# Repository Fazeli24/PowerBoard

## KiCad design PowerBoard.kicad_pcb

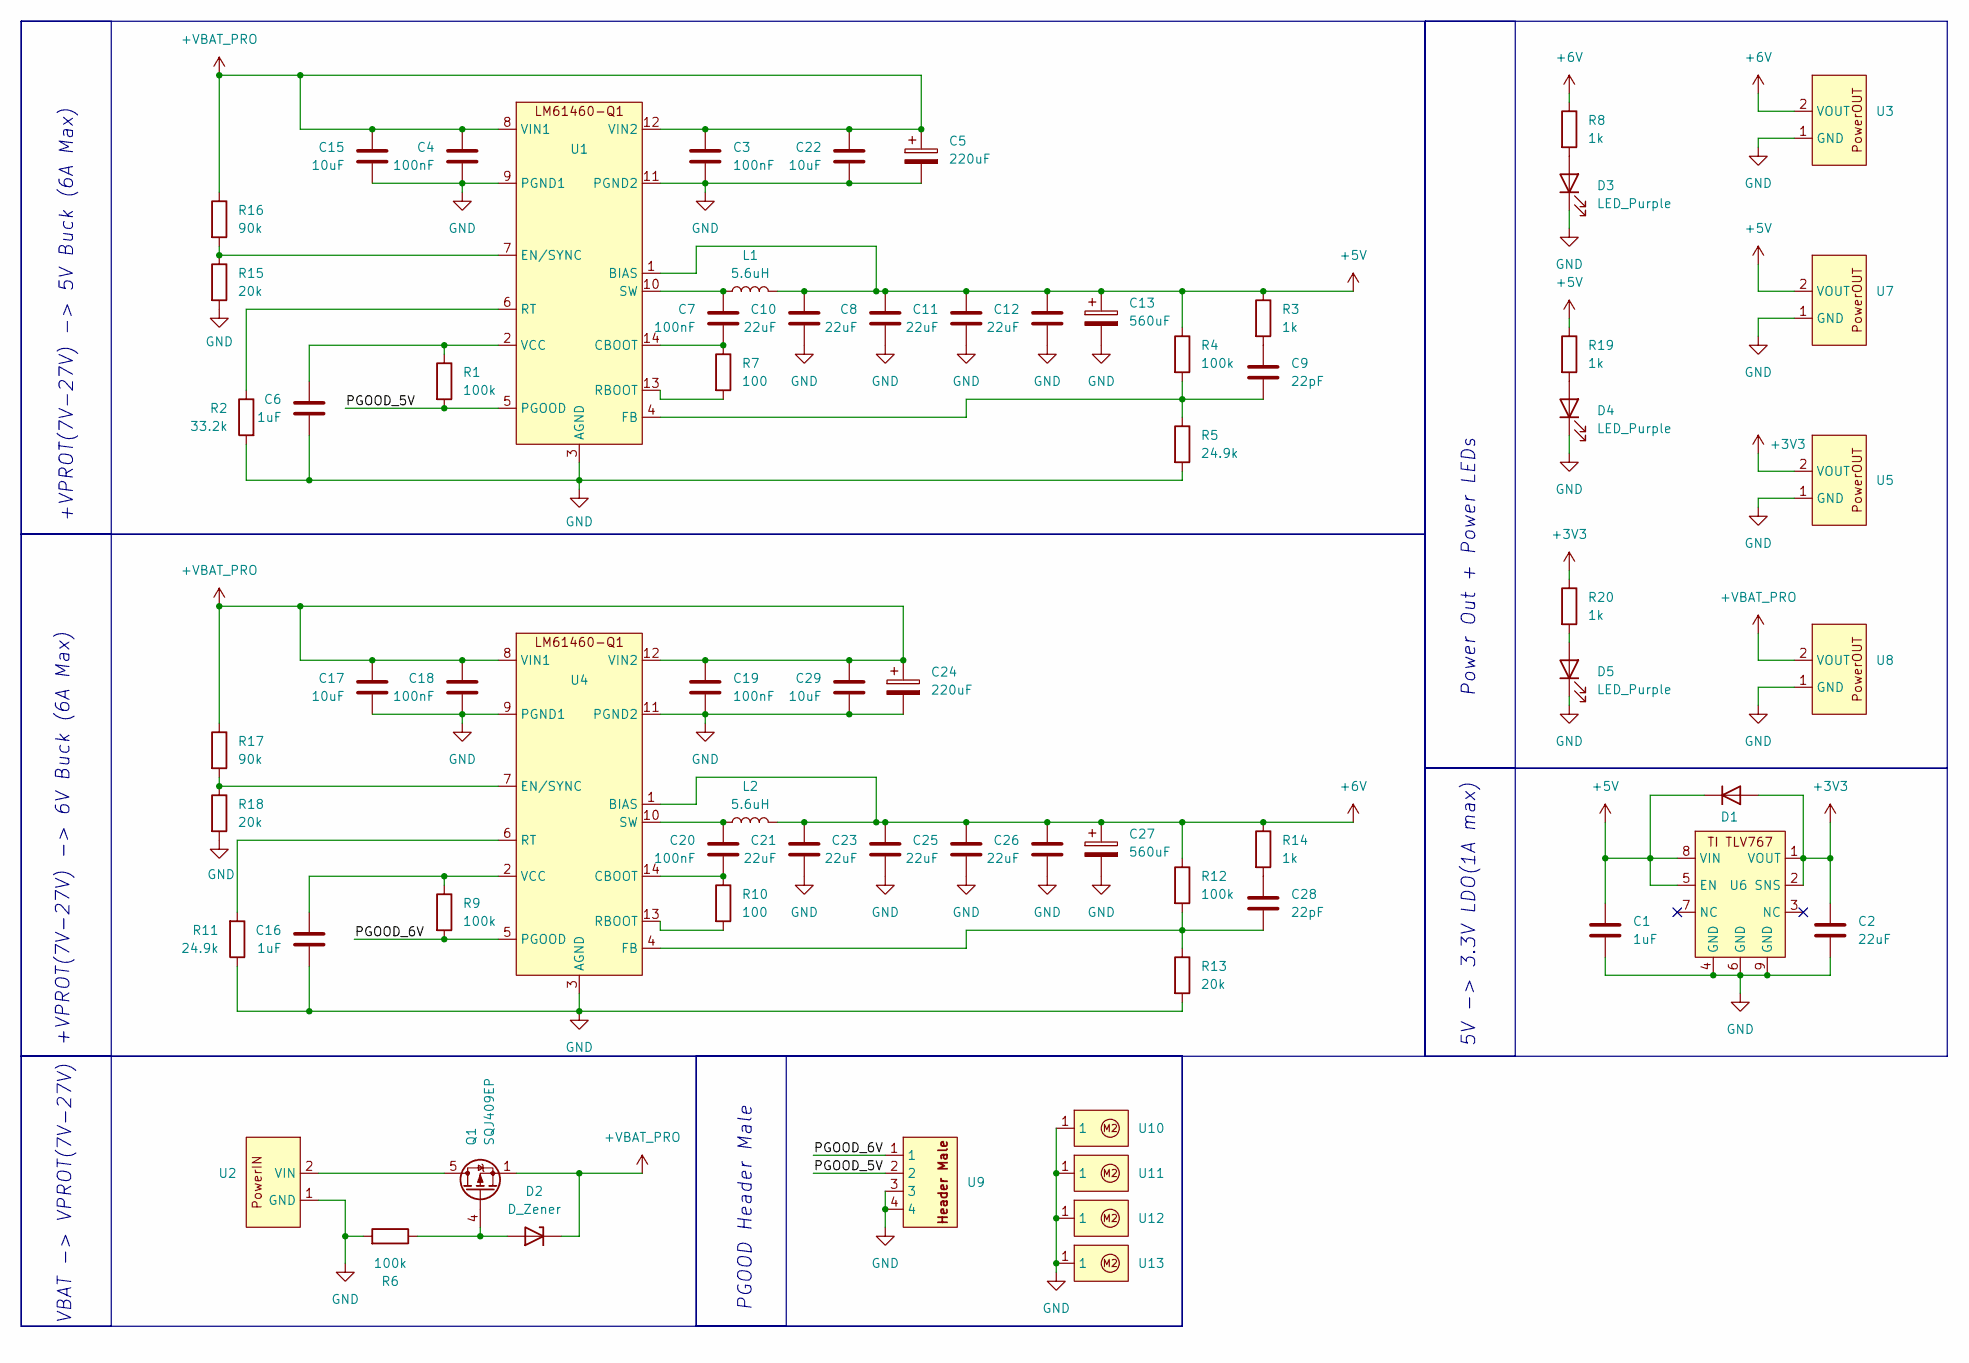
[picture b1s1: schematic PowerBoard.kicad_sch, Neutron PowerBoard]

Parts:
C1, C6, C16: 1uF; C_0603_1608Metric; LCSC Part # C59782
C2, C8, C10, C11, C12, C21, C23, C25, C26: 22uF; C_1210_3225Metric; LCSC Part # C55530
C3, C4, C7, C18, C19, C20: 100nF; C_0603_1608Metric; LCSC Part # C1591
C5, C24: 220uF; CP_Elec_8x10.5; LCSC Part # C278406
C9, C28: 22pF; C_0603_1608Metric; LCSC Part # C1653
C13, C27: 560uF; CP_Elec_8x10.5; LCSC Part # C497589
C15, C17, C22, C29: 10uF; C_1206_3216Metric; LCSC Part # C89632
D1: D; SOT-23-3; LCSC Part # C545546
D2: D_Zener; SOT-23; LCSC Part # C108437
D3, D4, D5: LED_Purple; LED_0603_1608Metric; LCSC Part # C7496831
L1, L2: 5.6uH; Inductor_11.5_10; LCSC Part # C49140770
Q1: SQJ409EP; PowerPAK_SO-8L_Single; LCSC Part # C727776
R1, R4, R6, R9, R12: 100k; R_0603_1608Metric; LCSC Part # C2906980
R2: 33.2k; R_0603_1608Metric; LCSC Part # C2933200
R3, R8, R14, R19, R20: 1k; R_0603_1608Metric; LCSC Part # C2907002
R5, R11: 24.9k; R_0603_1608Metric; LCSC Part # C2930080
R7, R10: 100; R_0603_1608Metric; LCSC Part # C2906981
R13, R15, R18: 20k; R_0603_1608Metric; LCSC Part # C2907011
R16, R17: 90k; R_0603_1608Metric; LCSC Part # C2907077
U1, U4: VQFN-HR14_RJR_TEX; LCSC Part # C2876600
U2, U3, U7, U8: HighCurrentPad
U5: LowCurrentPad
U6: HVSSOP-8-1EP_3x3mm_P0.65mm_EP1.57x1.89mm; LCSC Part # C2873382
U9: 4x1_2.54mmPitch
U10, U11, U12, U13: Unbenannt

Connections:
+3V3: C2.1, D1.2 (A), R20.1, U5.2 (VOUT), U6.1 (VOUT), U6.2 (SNS)
+5V: C1.1, C8.1, C10.1, C11.1, C12.1, C13.1, D1.1 (K), L1.2, R3.1, R4.1, R19.1, U1.1 (BIAS), U6.5 (EN), U6.8 (VIN), U7.2 (VOUT)
+6V: C21.1, C23.1, C25.1, C26.1, C27.1, L2.2, R8.1, R12.1, R14.1, U3.2 (VOUT), U4.1 (BIAS)
+VBAT_PRO: C3.1, C4.1, C5.1, C15.1, C17.1, C18.1, C19.1, C22.1, C24.1, C29.1, D2.1 (K), Q1.1 (S), Q1.2 (S), Q1.3 (S), R16.1, R17.1, U1.8 (VIN1), U1.12 (VIN2), U4.8 (VIN1), U4.12 (VIN2), U8.2 (VOUT)
/PGOOD_5V: R1.2, U1.5 (PGOOD), U9.2
/PGOOD_6V: R9.2, U4.5 (PGOOD), U9.1
GND: C1.2, C2.2, C3.2, C4.2, C5.2, C6.2, C8.2, C10.2, C11.2, C12.2, C13.2, C15.2, C16.2, C17.2, C18.2, C19.2, C21.2, C22.2, C23.2, C24.2, C25.2, C26.2, C27.2, C29.2, D3.1 (K), D4.1 (K), D5.1 (K), R2.2, R5.2, R6.2, R11.1, R13.2, R15.2, R18.2, U1.3 (AGND), U1.9 (PGND1), U1.11 (PGND2), U2.1 (GND), U3.1 (GND), U4.3 (AGND), U4.9 (PGND1), U4.11 (PGND2), U5.1 (GND), U6.4 (GND), U6.6 (GND), U6.9 (GND), U7.1 (GND), U8.1 (GND), U9.3, U9.4, U10.1 (1_1), U11.1 (1_1), U12.1 (1_1), U13.1 (1_1)
unnamed: C9.1, R3.2
unnamed: C28.1, R14.2
unnamed: D2.2 (A), Q1.4 (G), R6.1
unnamed: D3.2 (A), R8.2
unnamed: D4.2 (A), R19.2
unnamed: D5.2 (A), R20.2
unnamed: Q1.5 (D), U2.2 (VIN)
unnamed: C7.2, R7.1, U1.14 (CBOOT)
unnamed: R15.1, R16.2, U1.7 (EN/SYNC)
unnamed: C9.2, R4.2, R5.1, U1.4 (FB)
unnamed: R7.2, U1.13 (RBOOT)
unnamed: R2.1, U1.6 (RT)
unnamed: C7.1, L1.1, U1.10 (SW)
unnamed: C6.1, R1.1, U1.2 (VCC)
unnamed: C20.2, R10.1, U4.14 (CBOOT)
unnamed: R17.2, R18.1, U4.7 (EN/SYNC)
unnamed: C28.2, R12.2, R13.1, U4.4 (FB)
unnamed: R10.2, U4.13 (RBOOT)
unnamed: R11.2, U4.6 (RT)
unnamed: C20.1, L2.1, U4.10 (SW)
unnamed: C16.1, R9.1, U4.2 (VCC)

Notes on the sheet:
VBAT -> VPROT(7V-27V)
PGOOD Header Male
5V -> 3.3V LDO(1A max)
Power Out + Power LEDs
+VPROT(7V-27V) -> 5V Buck (6A Max)
+VPROT(7V-27V) -> 6V Buck (6A Max)

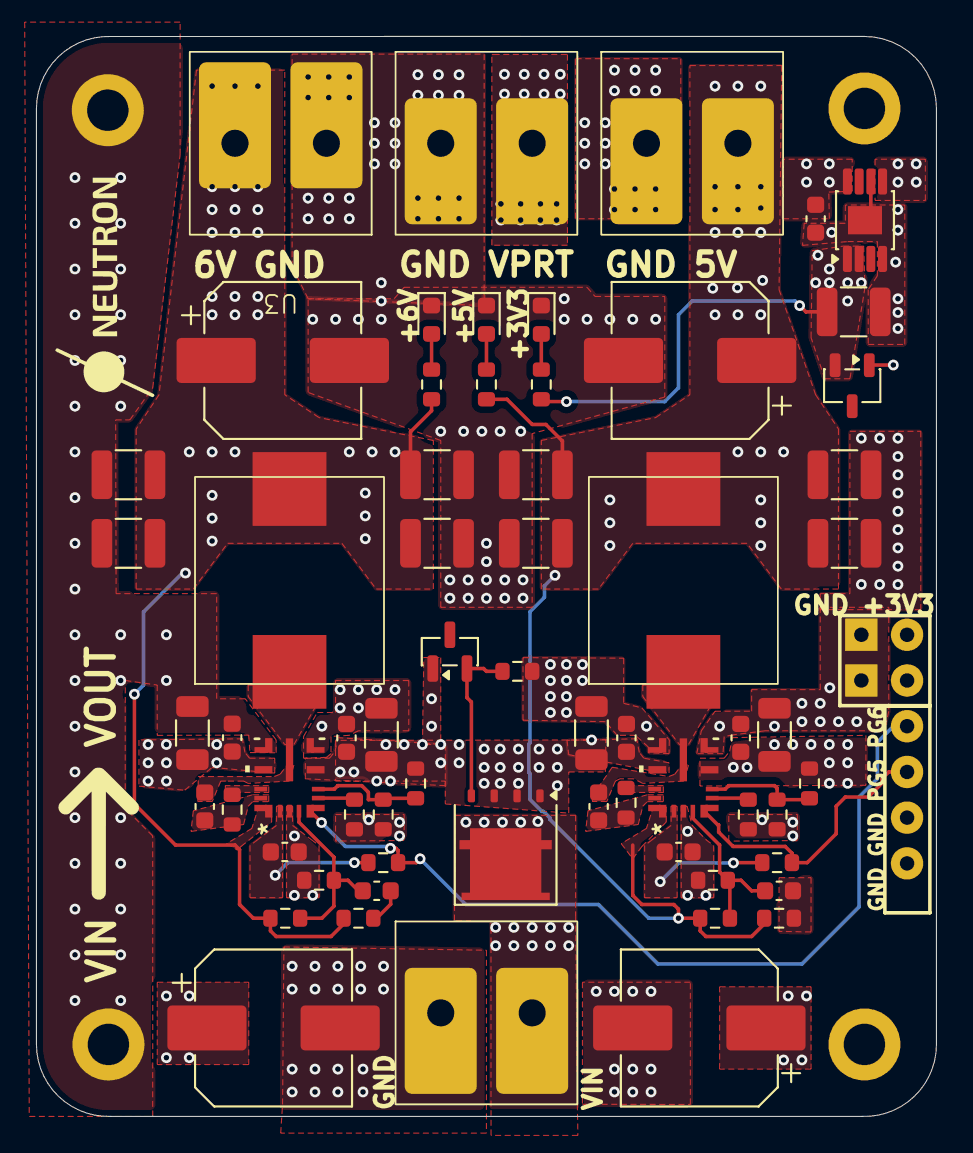
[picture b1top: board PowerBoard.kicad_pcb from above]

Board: 4 copper layers, 50.0 x 60.0 mm, 69 parts (0 on the bottom side), 28 nets.
